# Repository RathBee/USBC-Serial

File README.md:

A compact USB-C to UART bridge with independent UART IO power rail utlizing the CH343 chip

Main features:

  1.UART interface I/O powered independently, never worry about backfeeding again.

  2.High baud rate. Maximum speed up to 6Mbps.

  3.Supports USB CDC driver. No annoying driver instalation anymore.

  4.Correctly implemented USB-C port, you can use any cable you like.
  (some badly designed USB-C device tends to lack the two 5.1k pull-down resistor, or shorts two cc pin together, causing the device to become unusable when using certain C to C cables)

  5.Compact. (2cm x 2.6cm)

Warning: Do not try to power you external circuit with this board's 3.3V pin, the CH343's internal regulator can only handle 10mA of current.
Instead, this pin should only be used to power the CH343's internal UART transciver. 

You can short the 5V pin to the VIO pin to get 5V level UART output. It's the same for 3.3V.

You can also power the CH343's UART transciver using your own power supply, for example, your MCU's power supply(assuming you are connecting this board to a MCU).
This way, you can have arbitary UART voltage level ranging from 1.7V to 5.5V. And you don't have to worry about backfeeding.

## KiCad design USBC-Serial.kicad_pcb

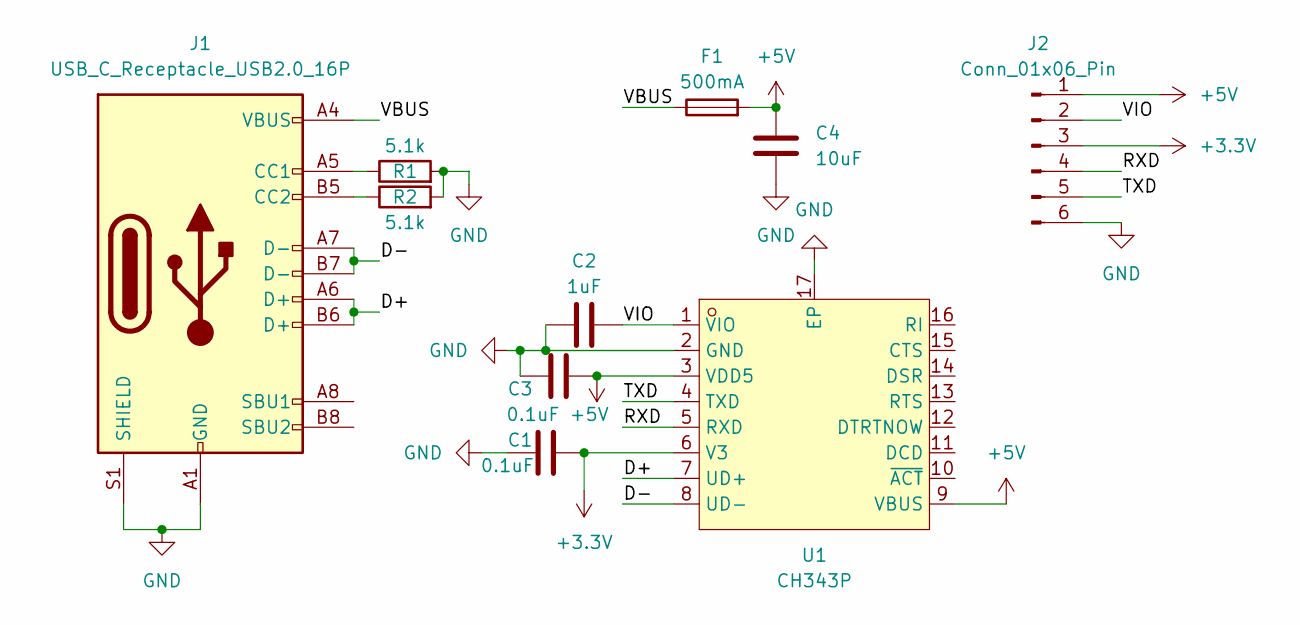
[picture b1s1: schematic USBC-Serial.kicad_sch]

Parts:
C1, C3: 0.1uF; C_0805_2012Metric
C2: 1uF; C_0805_2012Metric
C4: 10uF; C_0805_2012Metric
F1: 500mA; Fuse_1206_3216Metric
J1: USB_C_Receptacle_USB2.0_16P; USB_C_Receptacle_HRO_TYPE-C-31-M-12
J2: Conn_01x06_Pin; PinHeader_1x06_P2.54mm_Horizontal
R1, R2: 5.1k; R_0805_2012Metric
U1: CH343P; TQFN-16_L3.0-W3.0-P0.50-BL-EP1.7; LCSC Part C2846043

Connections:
+3.3V: C1.1, J2.3, U1.6 (V3)
+5V: C3.2, C4.1, F1.2, J2.1, U1.3 (VDD5), U1.9 (VBUS)
/D+: J1.A6 (D+), J1.B6 (D+), U1.7 (UD+)
/D-: J1.A7 (D-), J1.B7 (D-), U1.8 (UD-)
/RXD: J2.4, U1.5 (RXD)
/TXD: J2.5, U1.4 (TXD)
/VBUS: F1.1, J1.A4 (VBUS), J1.A9 (VBUS), J1.B4 (VBUS), J1.B9 (VBUS)
/VIO: C2.2, J2.2, U1.1 (VIO)
GND: C1.2, C2.1, C3.1, C4.2, J1.A1 (GND), J1.A12 (GND), J1.B1 (GND), J1.B12 (GND), J1.S1 (SHIELD), J2.6, R1.2, R2.2, U1.2 (GND), U1.17 (EP)
unnamed: J1.A5 (CC1), R1.1
unnamed: J1.B5 (CC2), R2.1

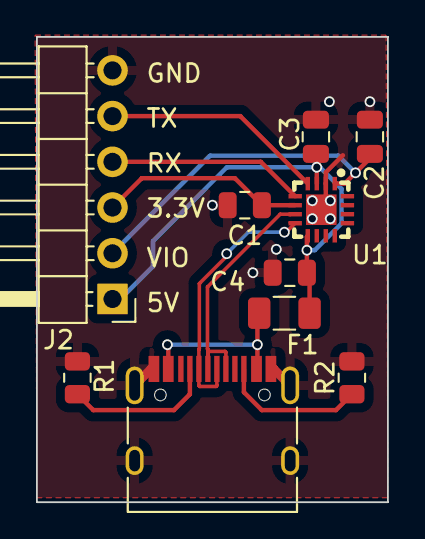
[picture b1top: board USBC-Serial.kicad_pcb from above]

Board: 2 copper layers, 19.5 x 25.9 mm, 10 parts (0 on the bottom side), 11 nets.

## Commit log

2024-02-07 Add license file
2024-02-07 add Type-C GND to shell connection
2024-02-07 remove offensive text
2024-02-07 add schematic image to README
2024-02-08 nuke everything - major refactor
2024-02-08 refactor, rotated the main chip for 90 degrees
2024-02-08 Redo D+ D- track, reroute R1 R2
2024-02-08 move J2 to the left, conserve some more space
2024-02-08 add text, delete old gerber files
2024-02-08 raret R1 and R2
2024-02-13 fix bypass caps' ground return path
2024-02-13 fix bypass caps
